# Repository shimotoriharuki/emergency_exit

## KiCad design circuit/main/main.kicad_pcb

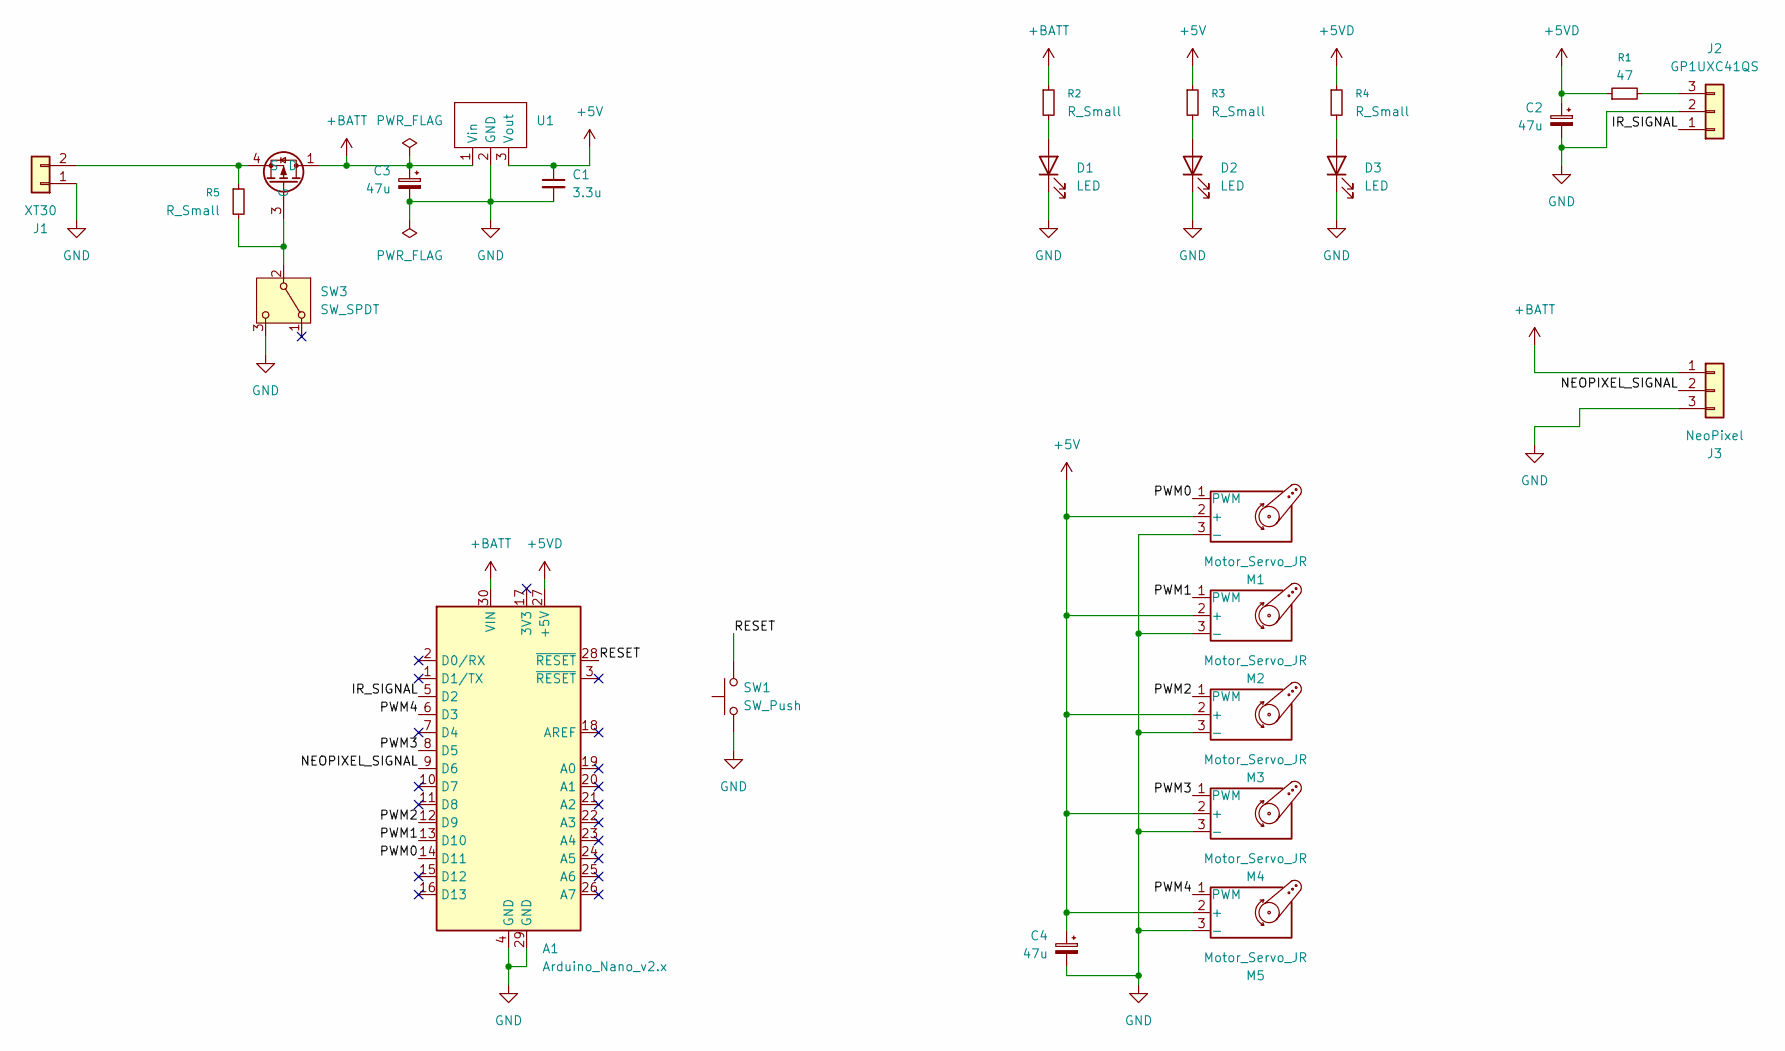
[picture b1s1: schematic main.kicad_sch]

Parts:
A1: Arduino_Nano_v2.x; Arduino_Nano
C1: 3.3u; C_0603_1608Metric_Pad1.08x0.95mm_HandSolder
C2, C3, C4: 47u; CP_Radial_D5.0mm_P2.00mm
D1, D2, D3: LED; LED_0603_1608Metric_Pad1.05x0.95mm_HandSolder
J1: XT30; AMASS_XT30PW-M_1x02_P2.50mm_Horizontal
J2: GP1UXC41QS; Vishay_MINICAST-3Pin
J3: NeoPixel; JST_PH_B3B-PH-K_1x03_P2.00mm_Vertical
M1, M2, M3, M4, M5: Motor_Servo_JR; PinHeader_1x03_P2.54mm_Vertical
R1: 47; R_0603_1608Metric_Pad0.98x0.95mm_HandSolder
R2, R3, R4, R5: R_Small; R_0603_1608Metric_Pad0.98x0.95mm_HandSolder
SW1: SW_Push; SW_PUSH-12mm
SW3: SW_SPDT; SW_Slide_SPDT_Angled_CK_OS102011MA1Q
U1: Converter_DCDC_M78AR05-1
U2: TSOP-6_1.65x3.05mm_P0.95mm

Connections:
+5V: C1.1, C4.1, M1.2 (+), M2.2 (+), M3.2 (+), M4.2 (+), M5.2 (+), R3.1, U1.3 (Vout)
+5VD: A1.27 (+5V), C2.1, R1.1, R4.1
+BATT: A1.30 (VIN), C3.1, J3.1, R2.1, U1.1 (Vin), U2.1 (D), U2.2 (D), U2.5 (D), U2.6 (D)
/IR_SIGNAL: A1.5 (D2), J2.1
/NEOPIXEL_SIGNAL: A1.9 (D6), J3.2
/PWM0: A1.14 (D11), M1.1 (PWM)
/PWM1: A1.13 (D10), M2.1 (PWM)
/PWM2: A1.12 (D9), M3.1 (PWM)
/PWM3: A1.8 (D5), M4.1 (PWM)
/PWM4: A1.6 (D3), M5.1 (PWM)
/RESET: A1.28 (~RESET), SW1.2
GND: A1.4 (GND), A1.29 (GND), C1.2, C2.2, C3.2, C4.2, D1.1 (K), D2.1 (K), D3.1 (K), J1.1, J2.2, J3.3, M1.3 (-), M2.3 (-), M3.3 (-), M4.3 (-), M5.3 (-), SW1.1, SW3.3 (C), U1.2 (GND)
unnamed: D1.2 (A), R2.2
unnamed: D2.2 (A), R3.2
unnamed: D3.2 (A), R4.2
unnamed: J1.2, R5.1, U2.4 (S)
unnamed: J2.3, R1.2
unnamed: R5.2, SW3.2 (B), U2.3 (G)

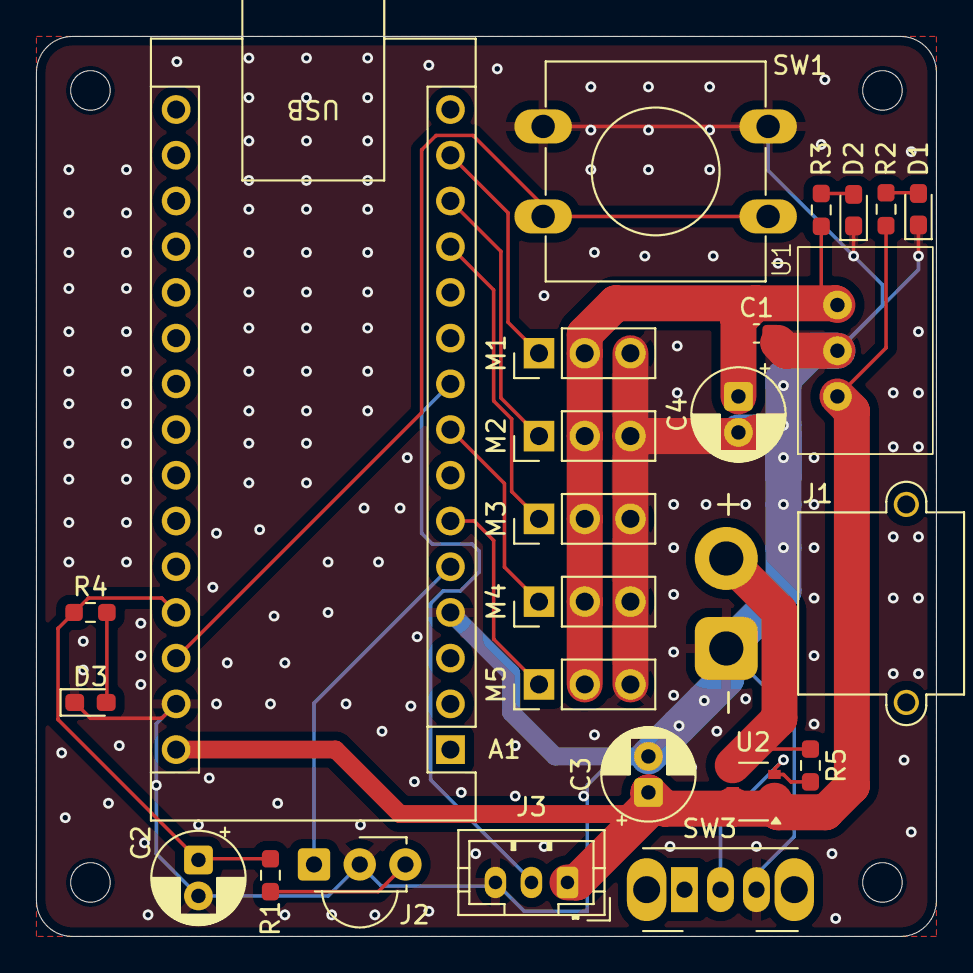
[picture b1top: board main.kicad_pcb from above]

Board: 2 copper layers, 50.0 x 50.0 mm, 25 parts (0 on the bottom side), 18 nets.

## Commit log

2025-04-18 書き込めた
2025-04-18 Create LICENSE
2025-04-18 ignore更新
2025-04-19 回路追加
2025-04-19 gitignore更新
2025-04-21 フットプリント割当
2025-04-26 パターン図
2025-04-26 step
